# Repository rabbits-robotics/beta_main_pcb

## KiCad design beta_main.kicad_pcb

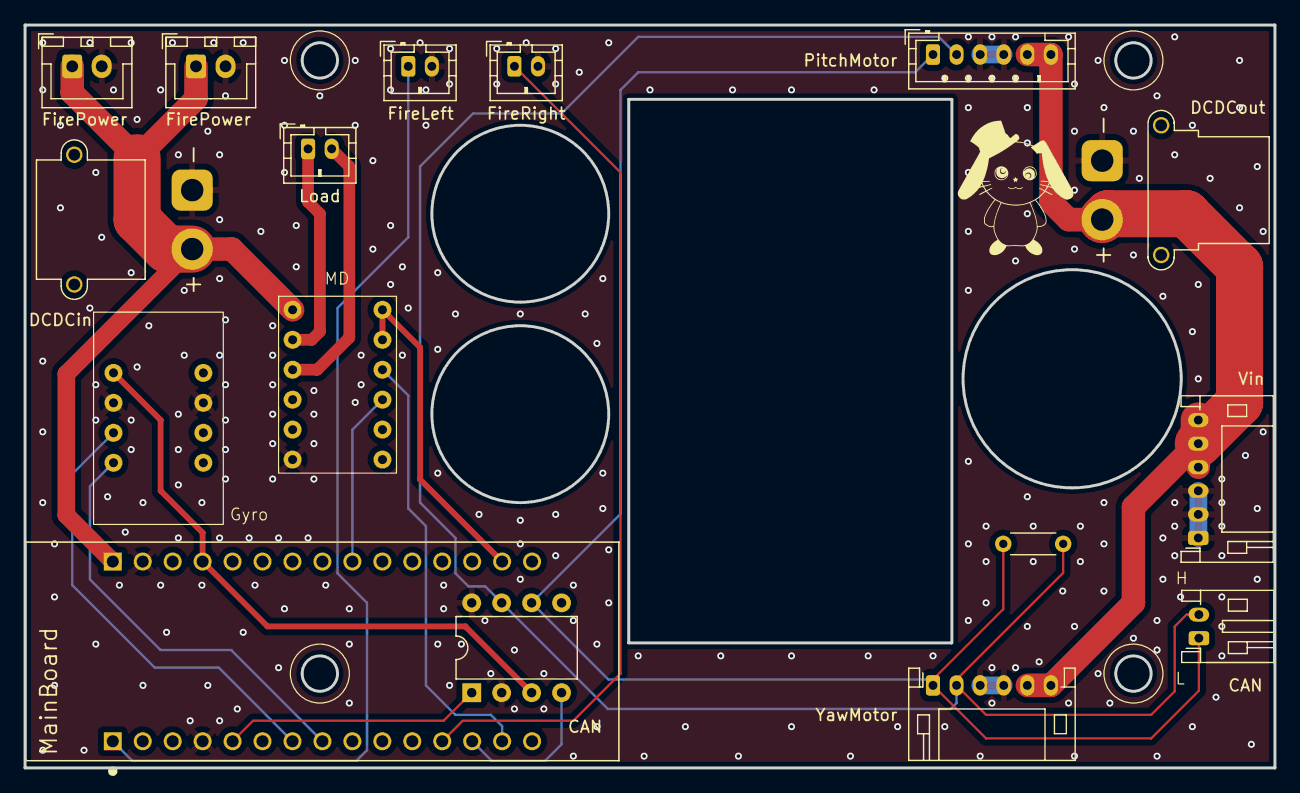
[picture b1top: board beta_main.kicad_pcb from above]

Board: 2 copper layers, 106.0 x 63.0 mm, 16 parts (0 on the bottom side), 17 nets.

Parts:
CAN: MCP2562-E-P; DIP-8_W7.62mm
CAN#2: Conn_01x02; JST_PH_S2B-PH-K_1x02_P2.00mm_Horizontal
DCDCin: Conn_01x02; AMASS_XT30PW-M_1x02_P2.50mm_Horizontal
DCDCout: Conn_01x02; AMASS_XT30PW-F_1x02_P2.50mm_Horizontal
FireLeft: Conn_01x02; JST_PH_B2B-PH-K_1x02_P2.00mm_Vertical
FirePower: Conn_01x02; JST_XH_B2B-XH-A_1x02_P2.50mm_Vertical
FirePower#2: Conn_01x02; JST_XH_B2B-XH-A_1x02_P2.50mm_Vertical
FireRight: Conn_01x02; JST_PH_B2B-PH-K_1x02_P2.00mm_Vertical
Gyro: BNO055
Load: Conn_01x02; JST_PH_B2B-PH-K_1x02_P2.00mm_Vertical
MD: DRV8835
MainBoard: NUCLEO-F303K8; MODULE_NUCLEO-F303K8
PitchMotor: Conn_01x06; JST_PH_B6B-PH-K_1x06_P2.00mm_Vertical
R1: 120; R_Axial_DIN0204_L3.6mm_D1.6mm_P5.08mm_Horizontal
Vin: Conn_01x06; JST_PH_S6B-PH-K_1x06_P2.00mm_Horizontal
YawMotor: Conn_01x06; JST_PH_S6B-PH-K_1x06_P2.00mm_Horizontal

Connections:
+3V3: MD.11 (MODE), MD.12 (VCC), MainBoard.4_14 (+3V3)
+5V: CAN.3 (VDD), Gyro.1 (VIN), MainBoard.4_4 (+5V)
+7.5V: DCDCin.2, FirePower.1, FirePower#2.1, MD.1 (VM), MainBoard.4_1 (VIN)
+24V: DCDCout.2, PitchMotor.5, PitchMotor.6, Vin.4, Vin.5, Vin.6, YawMotor.5, YawMotor.6
/CAN_H: CAN.7 (CANH), CAN#2.2, PitchMotor.2, R1.1, YawMotor.2
/CAN_L: CAN.6 (CANL), CAN#2.1, PitchMotor.1, R1.2, YawMotor.1
/CAN_RX: CAN.4 (RXD), MainBoard.3_13 (PA11)
/CAN_TX: CAN.1 (TXD), MainBoard.3_5 (PA12)
/FIRE_LEFT_MOTOR: FireLeft.1, MainBoard.3_1 (PA9)
/FIRE_RIGHT_MOTOR: FireRight.1, MainBoard.3_12 (PA8)
/I2C_SCL: Gyro.4 (SCL/R), MainBoard.3_8 (PB6)
/I2C_SDA: Gyro.3 (SDA/T), MainBoard.3_7 (PB7)
/LOAD_MOTOR_ENABLE: MD.9 (AIN2/AENBL), MainBoard.4_9 (PA4)
/LOAD_MOTOR_PHASE: MD.10 (AIN/APHASE), MainBoard.3_14 (PB5)
GND: CAN.2 (VSS), CAN.8 (STBY), DCDCin.1, DCDCout.1, FireLeft.2, FirePower.2, FirePower#2.2, FireRight.2, Gyro.2 (GND), Gyro.7 (GND), MD.6 (GND), MainBoard.3_4 (GND_1), MainBoard.4_2 (GND_2), PitchMotor.3, PitchMotor.4, Vin.1, Vin.2, Vin.3, YawMotor.3, YawMotor.4
unnamed: Load.1, MD.2 (AOUT1)
unnamed: Load.2, MD.3 (AOUT2)
